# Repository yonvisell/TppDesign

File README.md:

# Thermopneumatic tactile pixel display

A 3 × 3 fingertip display uses electrically heated air cavities to deflect a silicone membrane at selected pixels. A 6 V driver controls the passive tactile array through ten conductors.

Max Linnander, Yon Visell, “Thermopneumatic Pixels: Fast, Localized, Robust, Low-Voltage Touch Feedback,” *IEEE Transactions on Haptics*, 2026. [journal](https://ieeexplore.ieee.org/document/11771129) · [arxiv](https://arxiv.org/abs/2603.16750)

**[Owner design book (PDF)](Owner-design-book.pdf)** · Revision L. System specifications, assembly drawings, model-based temperature control, predicted pressure response and complete client API.

| Subsystem | Design files |
|---|---|
| Tactile array | [Drawings](head/TA-drawings.pdf) · [Full-size templates](head/Lab-templates-1to1.pdf) · [STEP models](head/Mechanical-CAD.zip) · [Fabrication packages](head/jobs) |
| Driver board | [Schematic](eb/Schematic.pdf) · [Assembly package](eb/EB-supplier.zip) · [Firmware and installation](firmware/Controller.md) |
| Client interface | [OSC over UDP](software/OSC.md) · [Python client](software/client.py). Unit 1 uses the address prefix `/tpp/ta/1`. |
| Purchasing | [Bill of materials](purchasing/Integrated-BOM.csv) · [Build budget](purchasing/Build-budget.xlsx) |

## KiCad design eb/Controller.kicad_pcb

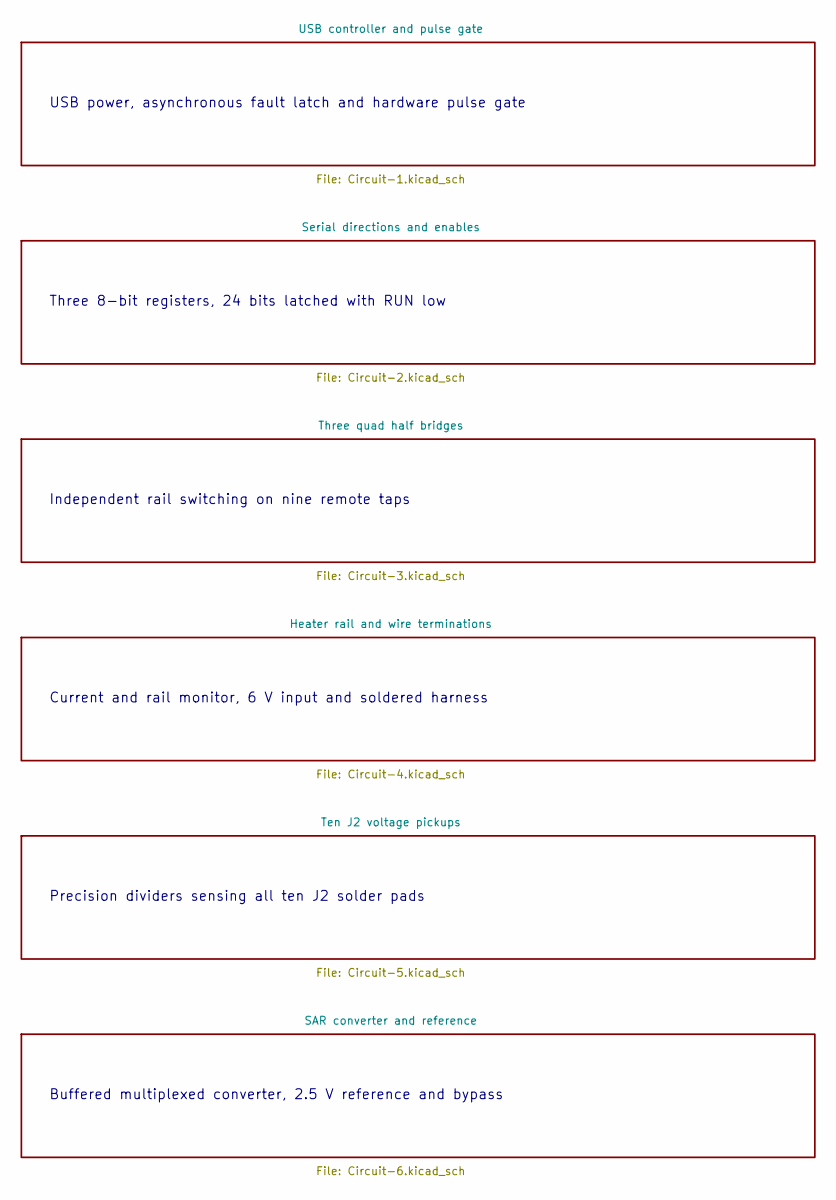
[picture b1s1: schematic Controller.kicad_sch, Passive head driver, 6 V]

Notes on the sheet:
USB power, asynchronous fault latch and hardware pulse gate
Three 8-bit registers, 24 bits latched with RUN low
Independent rail switching on nine remote taps
Current and rail monitor, 6 V input and soldered harness
Precision dividers sensing all ten J2 solder pads
Buffered multiplexed converter, 2.5 V reference and bypass

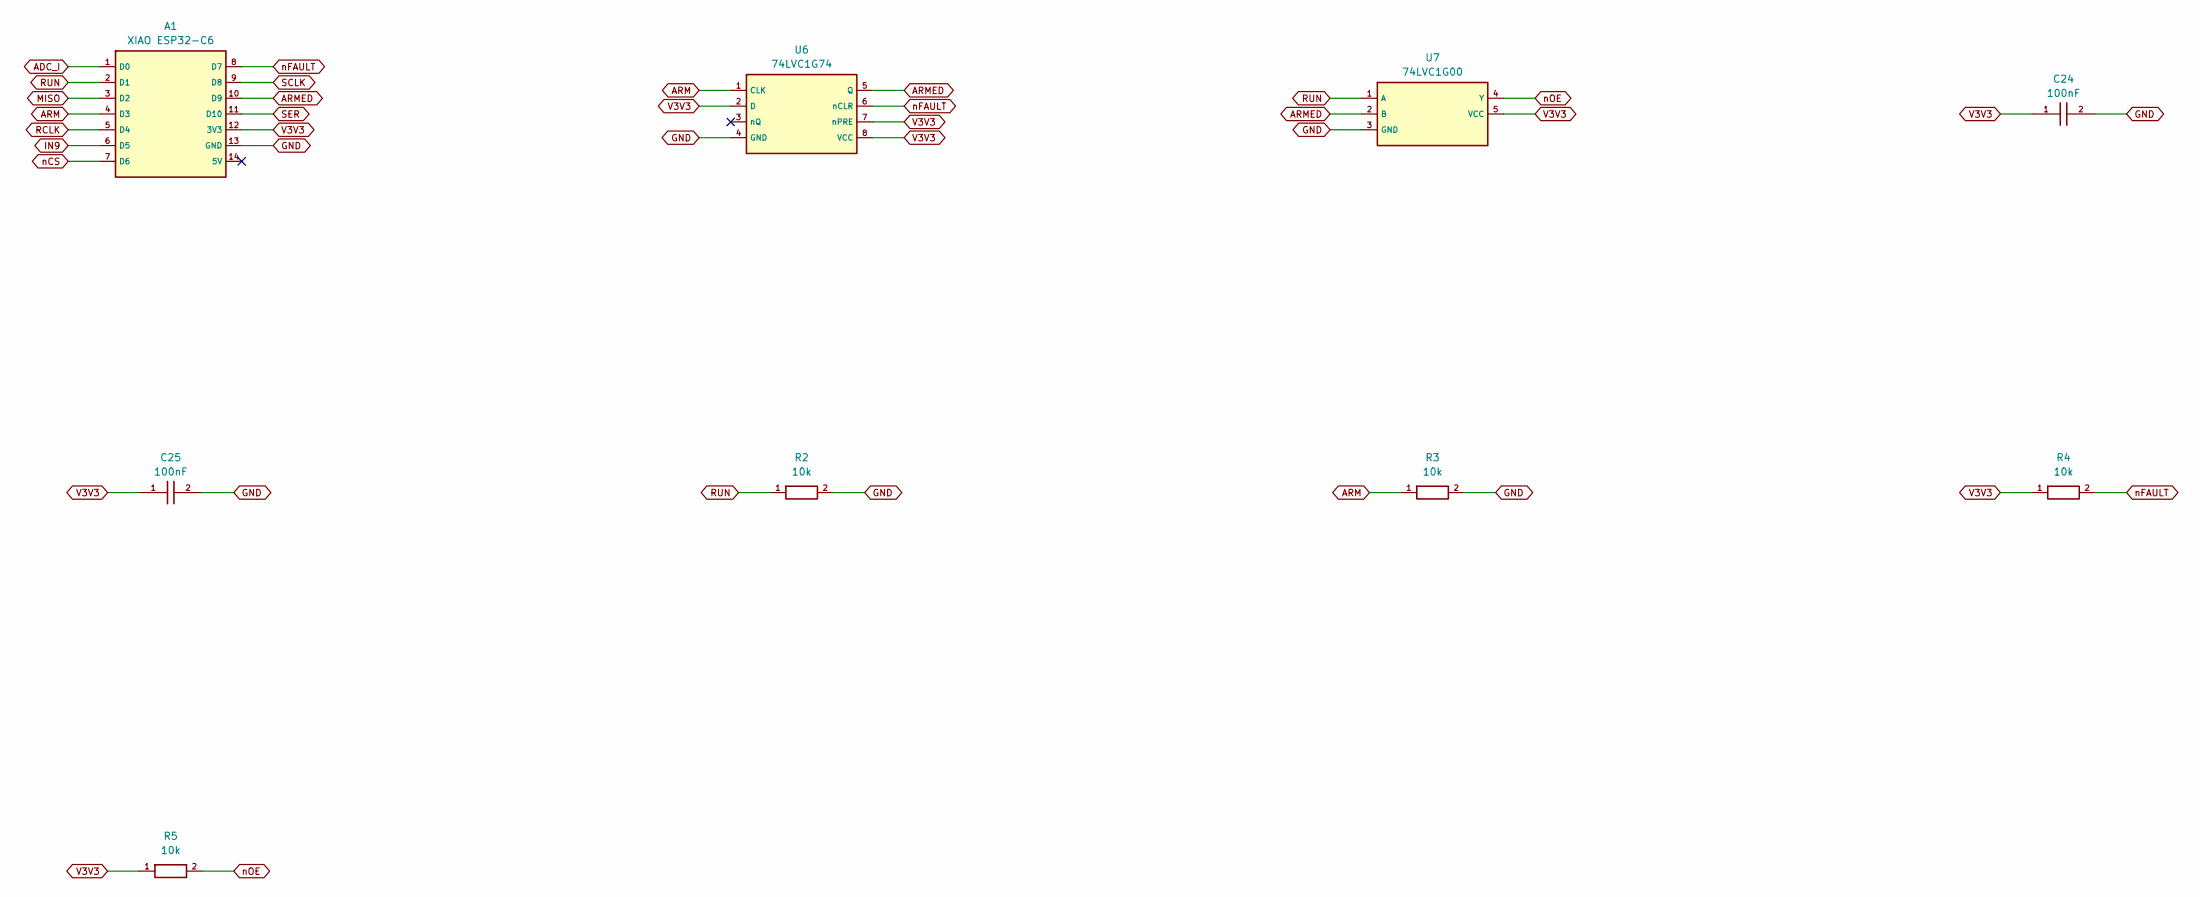
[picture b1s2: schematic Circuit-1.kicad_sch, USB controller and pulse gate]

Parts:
A1: XIAO ESP32-C6; XIAO-C6; MPN 113991254
C24, C25: 100nF; C_0603_1608Metric; MPN CC0603KRX7R9BB104
R2, R3, R4, R5: 10k; R_0603_1608Metric; MPN 0603WAF1002T5E
U6: 74LVC1G74; VSSOP-8_2.3x2mm_P0.5mm; MPN SN74LVC1G74DCUR
U7: 74LVC1G00; SOT-23-5; MPN SN74LVC1G00DBVR

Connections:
ADC_I: A1.1 (D0); also elsewhere on the board
ARM: A1.4 (D3), R3.1, U6.1 (CLK)
ARMED: A1.10 (D9), U6.5 (Q), U7.2 (B)
GND: A1.13 (GND), C24.2, C25.2, R2.2, R3.2, U6.4 (GND), U7.3 (GND); also elsewhere on the board
IN9: A1.6 (D5); also elsewhere on the board
MISO: A1.3 (D2); also elsewhere on the board
RCLK: A1.5 (D4); also elsewhere on the board
RUN: A1.2 (D1), R2.1, U7.1 (A)
SCLK: A1.9 (D8); also elsewhere on the board
SER: A1.11 (D10); also elsewhere on the board
V3V3: A1.12 (3V3), C24.1, C25.1, R4.1, R5.1, U6.2 (D), U6.7 (nPRE), U6.8 (VCC), U7.5 (VCC); also elsewhere on the board
nCS: A1.7 (D6); also elsewhere on the board
nFAULT: A1.8 (D7), R4.2, U6.6 (nCLR); also elsewhere on the board
nOE: R5.2, U7.4 (Y); also elsewhere on the board

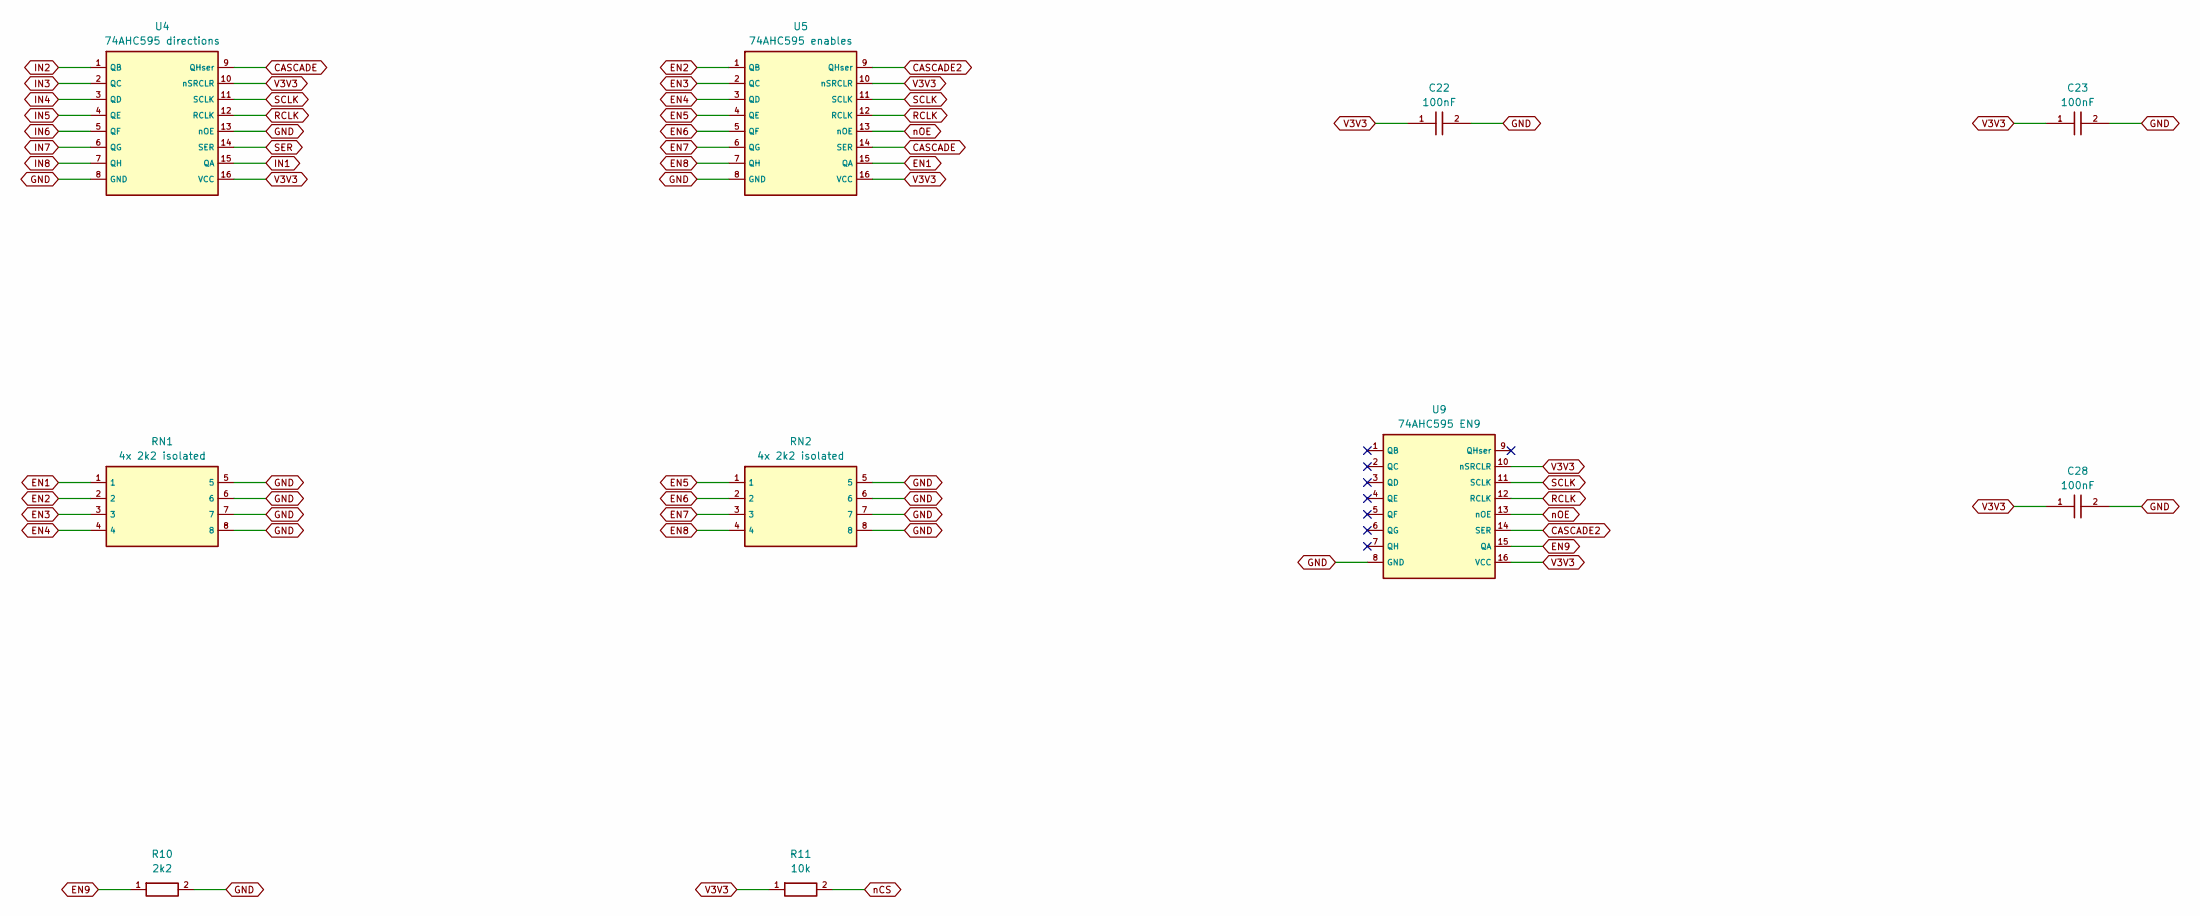
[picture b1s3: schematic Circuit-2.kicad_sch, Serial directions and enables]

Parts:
C22, C23, C28: 100nF; C_0603_1608Metric; MPN CC0603KRX7R9BB104
R10: 2k2; R_0603_1608Metric; MPN 0603WAF2201T5E
R11: 10k; R_0603_1608Metric; MPN 0603WAF1002T5E
RN1, RN2: 4x 2k2 isolated; R_Array_Convex_4x0603; MPN YC164-FR-072K2L
U4: 74AHC595 directions; TSSOP-16_4.4x5mm_P0.65mm; MPN SN74AHC595PWR
U5: 74AHC595 enables; TSSOP-16_4.4x5mm_P0.65mm; MPN SN74AHC595PWR
U9: 74AHC595 EN9; TSSOP-16_4.4x5mm_P0.65mm; MPN SN74AHC595PWR

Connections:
CASCADE: U4.9 (QHser), U5.14 (SER)
CASCADE2: U5.9 (QHser), U9.14 (SER)
EN1: RN1.1, U5.15 (QA); also elsewhere on the board
EN2: RN1.2, U5.1 (QB); also elsewhere on the board
EN3: RN1.3, U5.2 (QC); also elsewhere on the board
EN4: RN1.4, U5.3 (QD); also elsewhere on the board
EN5: RN2.1, U5.4 (QE); also elsewhere on the board
EN6: RN2.2, U5.5 (QF); also elsewhere on the board
EN7: RN2.3, U5.6 (QG); also elsewhere on the board
EN8: RN2.4, U5.7 (QH); also elsewhere on the board
EN9: R10.1, U9.15 (QA); also elsewhere on the board
GND: C22.2, C23.2, C28.2, R10.2, RN1.5, RN1.6, RN1.7, RN1.8, RN2.5, RN2.6, RN2.7, RN2.8, U4.8 (GND), U4.13 (nOE), U5.8 (GND), U9.8 (GND); also elsewhere on the board
IN1: U4.15 (QA); also elsewhere on the board
IN2: U4.1 (QB); also elsewhere on the board
IN3: U4.2 (QC); also elsewhere on the board
IN4: U4.3 (QD); also elsewhere on the board
IN5: U4.4 (QE); also elsewhere on the board
IN6: U4.5 (QF); also elsewhere on the board
IN7: U4.6 (QG); also elsewhere on the board
IN8: U4.7 (QH); also elsewhere on the board
RCLK: U4.12 (RCLK), U5.12 (RCLK), U9.12 (RCLK); also elsewhere on the board
SCLK: U4.11 (SCLK), U5.11 (SCLK), U9.11 (SCLK); also elsewhere on the board
SER: U4.14 (SER); also elsewhere on the board
V3V3: C22.1, C23.1, C28.1, R11.1, U4.10 (nSRCLR), U4.16 (VCC), U5.10 (nSRCLR), U5.16 (VCC), U9.10 (nSRCLR), U9.16 (VCC); also elsewhere on the board
nCS: R11.2; also elsewhere on the board
nOE: U5.13 (nOE), U9.13 (nOE); also elsewhere on the board

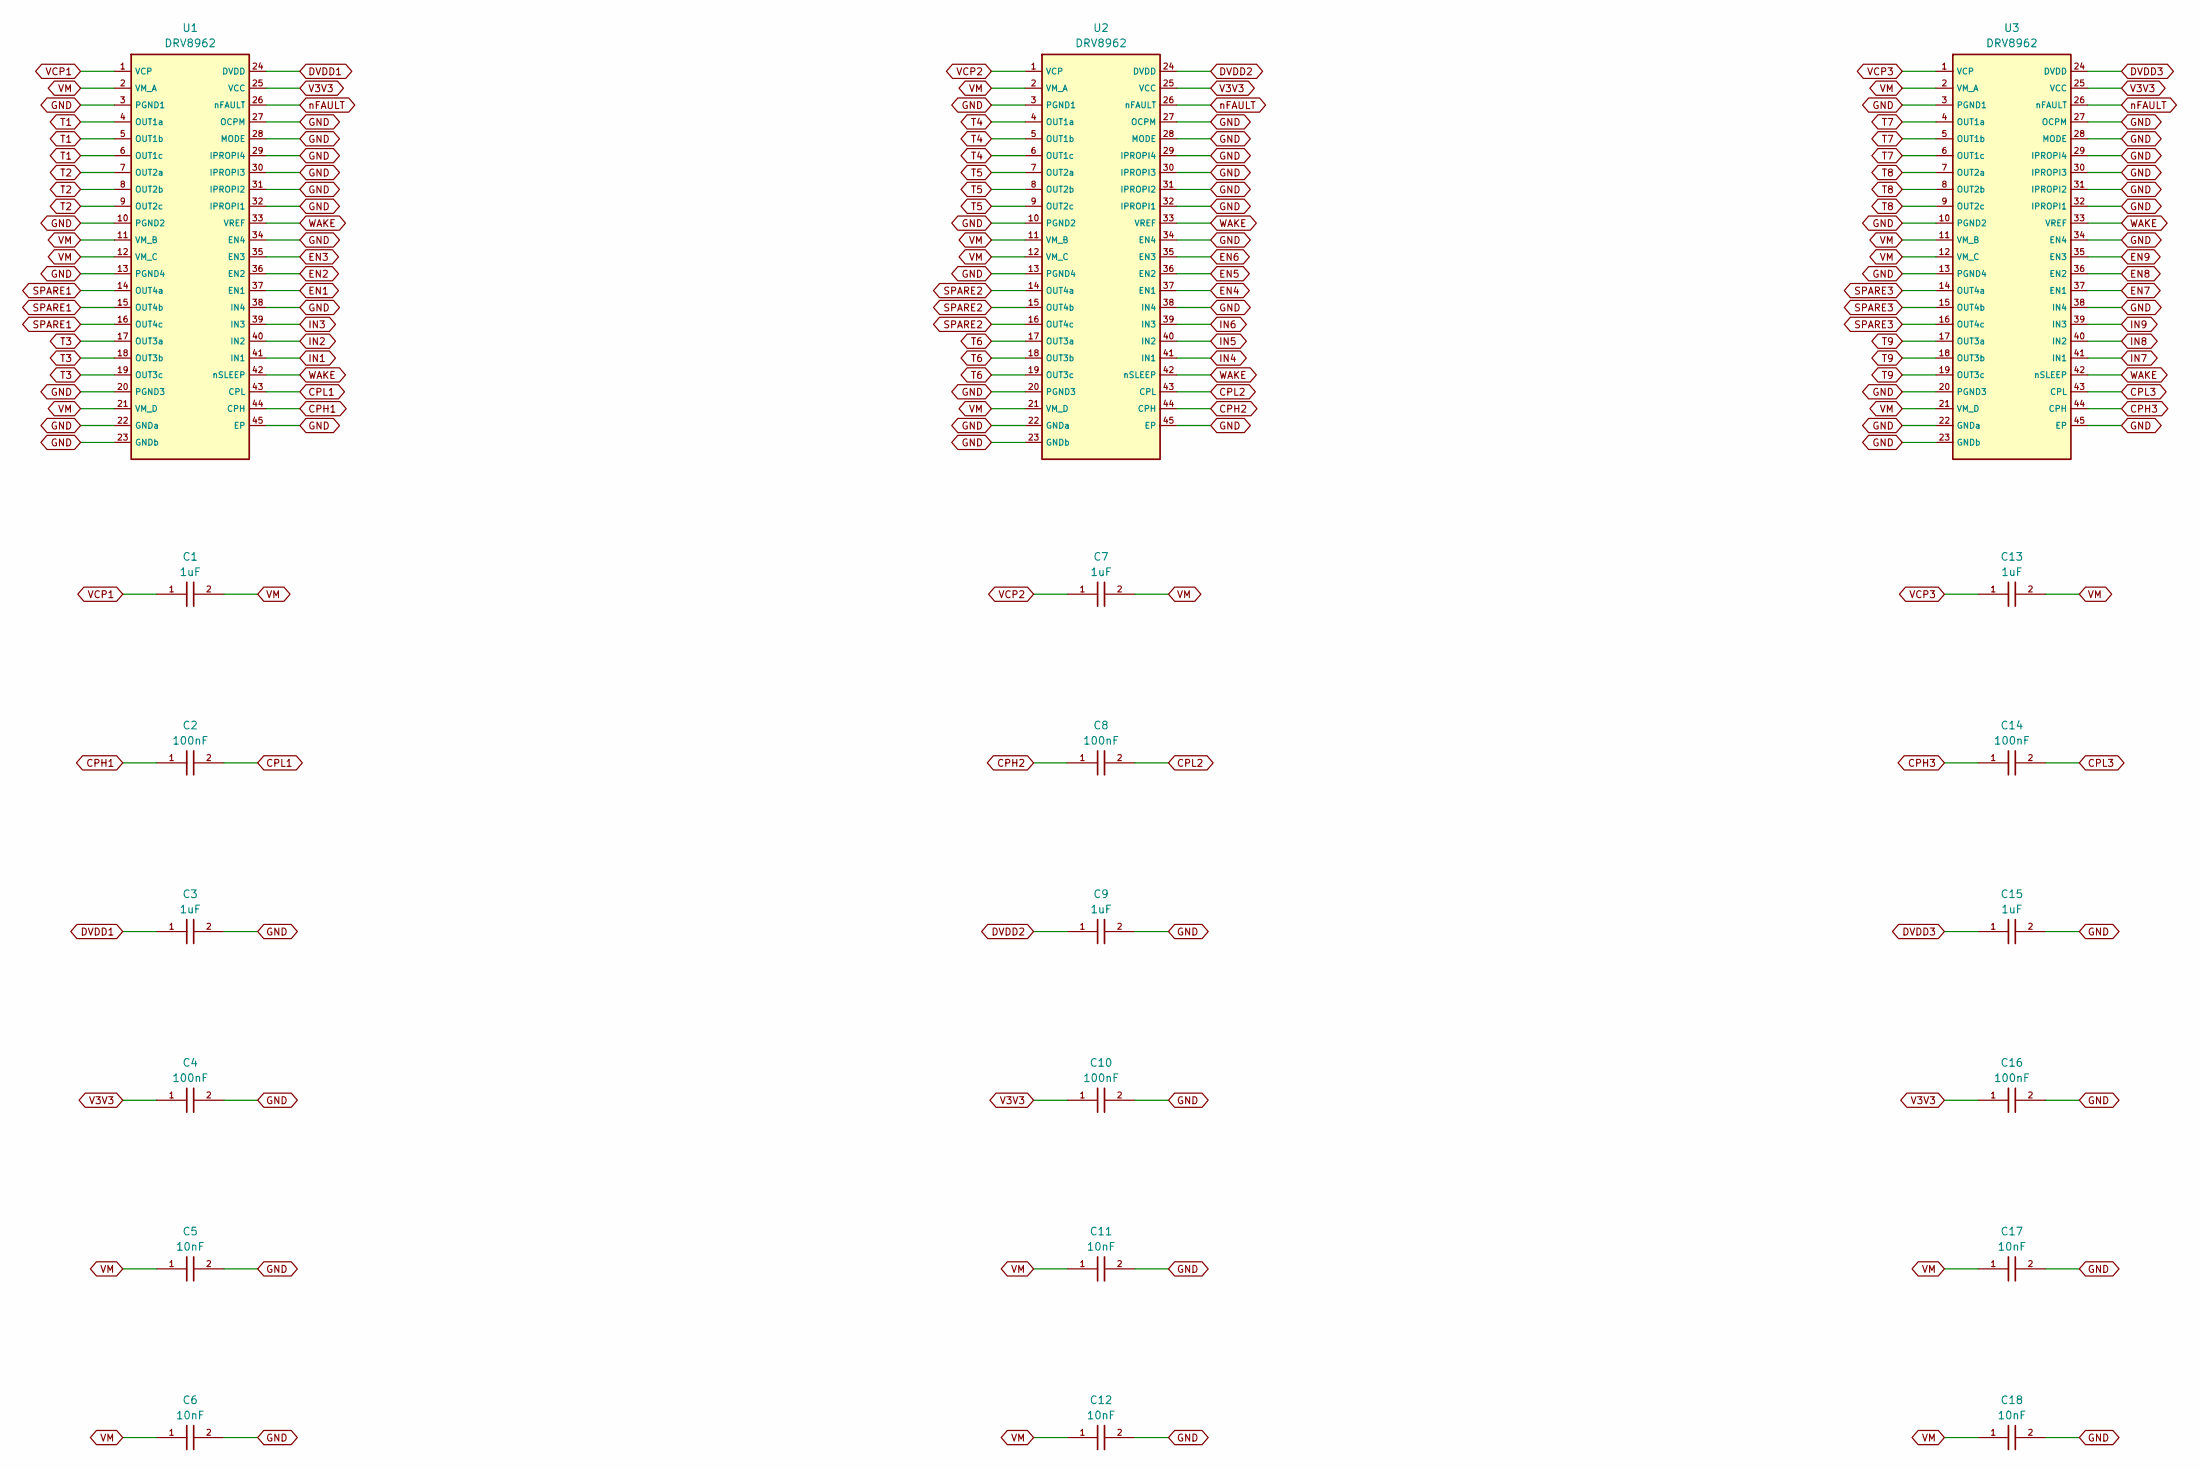
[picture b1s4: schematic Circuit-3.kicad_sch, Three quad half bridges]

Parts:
C1, C3, C7, C9, C13, C15: 1uF; C_0603_1608Metric; MPN CC0603KRX7R7BB105
C2, C4, C8, C10, C14, C16: 100nF; C_0603_1608Metric; MPN CC0603KRX7R9BB104
C5, C6, C11, C12, C17, C18: 10nF; C_0603_1608Metric; MPN GRM188R71H103KA01D
U1, U2, U3: DRV8962; DDW0044E; MPN DRV8962DDWR

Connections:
CPH1: C2.1, U1.44 (CPH)
CPH2: C8.1, U2.44 (CPH)
CPH3: C14.1, U3.44 (CPH)
CPL1: C2.2, U1.43 (CPL)
CPL2: C8.2, U2.43 (CPL)
CPL3: C14.2, U3.43 (CPL)
DVDD1: C3.1, U1.24 (DVDD)
DVDD2: C9.1, U2.24 (DVDD)
DVDD3: C15.1, U3.24 (DVDD)
EN1: U1.37 (EN1); also elsewhere on the board
EN2: U1.36 (EN2); also elsewhere on the board
EN3: U1.35 (EN3); also elsewhere on the board
EN4: U2.37 (EN1); also elsewhere on the board
EN5: U2.36 (EN2); also elsewhere on the board
EN6: U2.35 (EN3); also elsewhere on the board
EN7: U3.37 (EN1); also elsewhere on the board
EN8: U3.36 (EN2); also elsewhere on the board
EN9: U3.35 (EN3); also elsewhere on the board
GND: C3.2, C4.2, C5.2, C6.2, C9.2, C10.2, C11.2, C12.2, C15.2, C16.2, C17.2, C18.2, U1.3 (PGND1), U1.10 (PGND2), U1.13 (PGND4), U1.20 (PGND3), U1.22 (GNDa), U1.23 (GNDb), U1.27 (OCPM), U1.28 (MODE), U1.29 (IPROPI4), U1.30 (IPROPI3), U1.31 (IPROPI2), U1.32 (IPROPI1), U1.34 (EN4), U1.38 (IN4), U1.45 (EP), U2.3 (PGND1), U2.10 (PGND2), U2.13 (PGND4), U2.20 (PGND3), U2.22 (GNDa), U2.23 (GNDb), U2.27 (OCPM), U2.28 (MODE), U2.29 (IPROPI4), U2.30 (IPROPI3), U2.31 (IPROPI2), U2.32 (IPROPI1), U2.34 (EN4), U2.38 (IN4), U2.45 (EP), U3.3 (PGND1), U3.10 (PGND2), U3.13 (PGND4), U3.20 (PGND3), U3.22 (GNDa), U3.23 (GNDb), U3.27 (OCPM), U3.28 (MODE), U3.29 (IPROPI4), U3.30 (IPROPI3), U3.31 (IPROPI2), U3.32 (IPROPI1), U3.34 (EN4), U3.38 (IN4), U3.45 (EP); also elsewhere on the board
IN1: U1.41 (IN1); also elsewhere on the board
IN2: U1.40 (IN2); also elsewhere on the board
IN3: U1.39 (IN3); also elsewhere on the board
IN4: U2.41 (IN1); also elsewhere on the board
IN5: U2.40 (IN2); also elsewhere on the board
IN6: U2.39 (IN3); also elsewhere on the board
IN7: U3.41 (IN1); also elsewhere on the board
IN8: U3.40 (IN2); also elsewhere on the board
IN9: U3.39 (IN3); also elsewhere on the board
SPARE1: U1.14 (OUT4a), U1.15 (OUT4b), U1.16 (OUT4c)
SPARE2: U2.14 (OUT4a), U2.15 (OUT4b), U2.16 (OUT4c)
SPARE3: U3.14 (OUT4a), U3.15 (OUT4b), U3.16 (OUT4c)
T1: U1.4 (OUT1a), U1.5 (OUT1b), U1.6 (OUT1c); also elsewhere on the board
T2: U1.7 (OUT2a), U1.8 (OUT2b), U1.9 (OUT2c); also elsewhere on the board
T3: U1.17 (OUT3a), U1.18 (OUT3b), U1.19 (OUT3c); also elsewhere on the board
T4: U2.4 (OUT1a), U2.5 (OUT1b), U2.6 (OUT1c); also elsewhere on the board
T5: U2.7 (OUT2a), U2.8 (OUT2b), U2.9 (OUT2c); also elsewhere on the board
T6: U2.17 (OUT3a), U2.18 (OUT3b), U2.19 (OUT3c); also elsewhere on the board
T7: U3.4 (OUT1a), U3.5 (OUT1b), U3.6 (OUT1c); also elsewhere on the board
T8: U3.7 (OUT2a), U3.8 (OUT2b), U3.9 (OUT2c); also elsewhere on the board
T9: U3.17 (OUT3a), U3.18 (OUT3b), U3.19 (OUT3c); also elsewhere on the board
V3V3: C4.1, C10.1, C16.1, U1.25 (VCC), U2.25 (VCC), U3.25 (VCC); also elsewhere on the board
VCP1: C1.1, U1.1 (VCP)
VCP2: C7.1, U2.1 (VCP)
VCP3: C13.1, U3.1 (VCP)
VM: C1.2, C5.1, C6.1, C7.2, C11.1, C12.1, C13.2, C17.1, C18.1, U1.2 (VM_A), U1.11 (VM_B), U1.12 (VM_C), U1.21 (VM_D), U2.2 (VM_A), U2.11 (VM_B), U2.12 (VM_C), U2.21 (VM_D), U3.2 (VM_A), U3.11 (VM_B), U3.12 (VM_C), U3.21 (VM_D); also elsewhere on the board
WAKE: U1.33 (VREF), U1.42 (nSLEEP), U2.33 (VREF), U2.42 (nSLEEP), U3.33 (VREF), U3.42 (nSLEEP); also elsewhere on the board
nFAULT: U1.26 (nFAULT), U2.26 (nFAULT), U3.26 (nFAULT); also elsewhere on the board

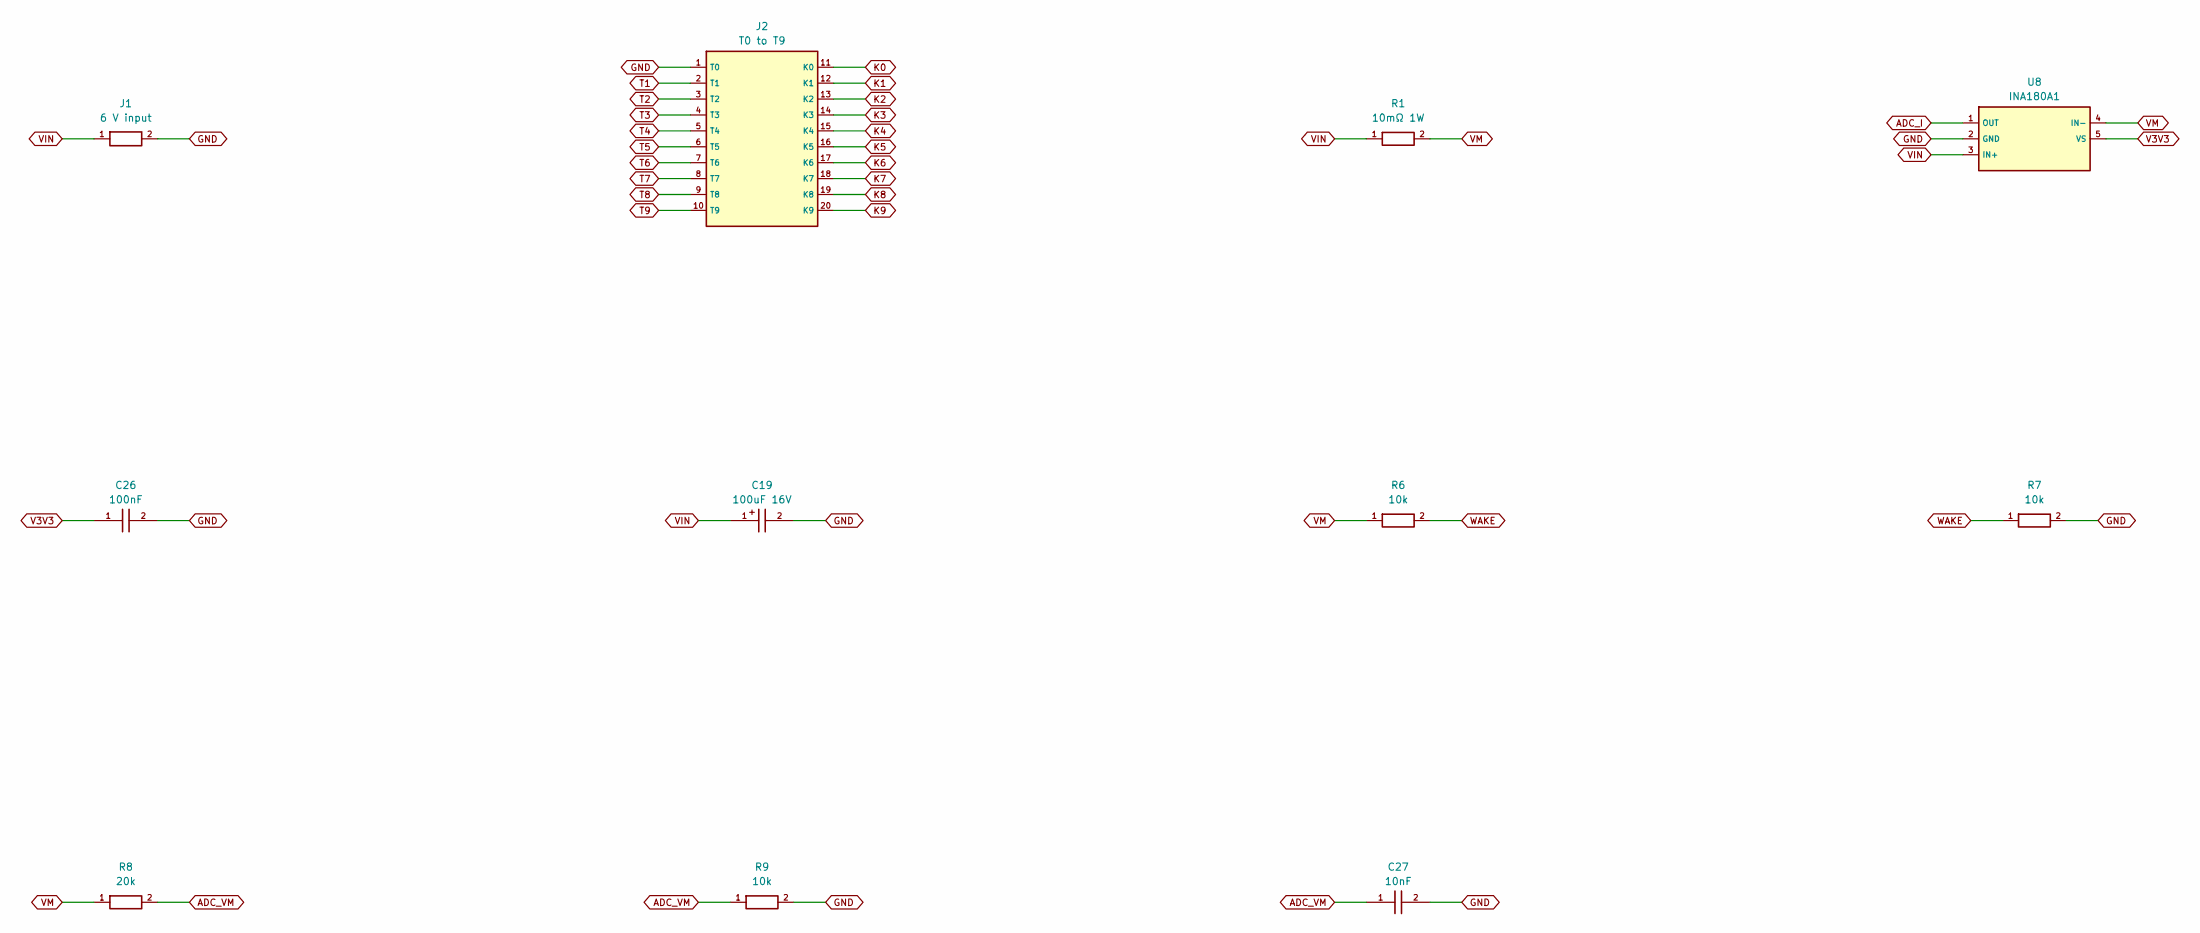
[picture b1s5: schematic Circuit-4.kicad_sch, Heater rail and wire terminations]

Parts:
C19: 100uF 16V; CP_Elec_6.3x5.8; MPN EEEFK1C101P
C26: 100nF; C_0603_1608Metric; MPN CC0603KRX7R9BB104
C27: 10nF; C_0603_1608Metric; MPN GRM188R71H103KA01D
J1: 6 V input; Power2; MPN PCB solder holes
J2: T0 to T9; Taps10; MPN PCB solder holes
R1: 10mΩ 1W; R_2512_6332Metric; MPN WSL2512R0100FEA
R6, R7, R9: 10k; R_0603_1608Metric; MPN 0603WAF1002T5E
R8: 20k; R_0603_1608Metric; MPN 0603WAF2002T5E
U8: INA180A1; SOT-23-5; MPN INA180A1IDBVR

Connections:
ADC_I: U8.1 (OUT); also elsewhere on the board
ADC_VM: C27.1, R8.2, R9.1; also elsewhere on the board
GND: C19.2 (-), C26.2, C27.2, J1.2 (RETURN), J2.1 (T0), R7.2, R9.2, U8.2 (GND); also elsewhere on the board
K0: J2.11 (K0); also elsewhere on the board
K1: J2.12 (K1); also elsewhere on the board
K2: J2.13 (K2); also elsewhere on the board
K3: J2.14 (K3); also elsewhere on the board
K4: J2.15 (K4); also elsewhere on the board
K5: J2.16 (K5); also elsewhere on the board
K6: J2.17 (K6); also elsewhere on the board
K7: J2.18 (K7); also elsewhere on the board
K8: J2.19 (K8); also elsewhere on the board
K9: J2.20 (K9); also elsewhere on the board
T1: J2.2 (T1); also elsewhere on the board
T2: J2.3 (T2); also elsewhere on the board
T3: J2.4 (T3); also elsewhere on the board
T4: J2.5 (T4); also elsewhere on the board
T5: J2.6 (T5); also elsewhere on the board
T6: J2.7 (T6); also elsewhere on the board
T7: J2.8 (T7); also elsewhere on the board
T8: J2.9 (T8); also elsewhere on the board
T9: J2.10 (T9); also elsewhere on the board
V3V3: C26.1, U8.5 (VS); also elsewhere on the board
VIN: C19.1 (+), J1.1 (PLUS), R1.1, U8.3 (IN+)
VM: R1.2, R6.1, R8.1, U8.4 (IN-); also elsewhere on the board
WAKE: R6.2, R7.1; also elsewhere on the board

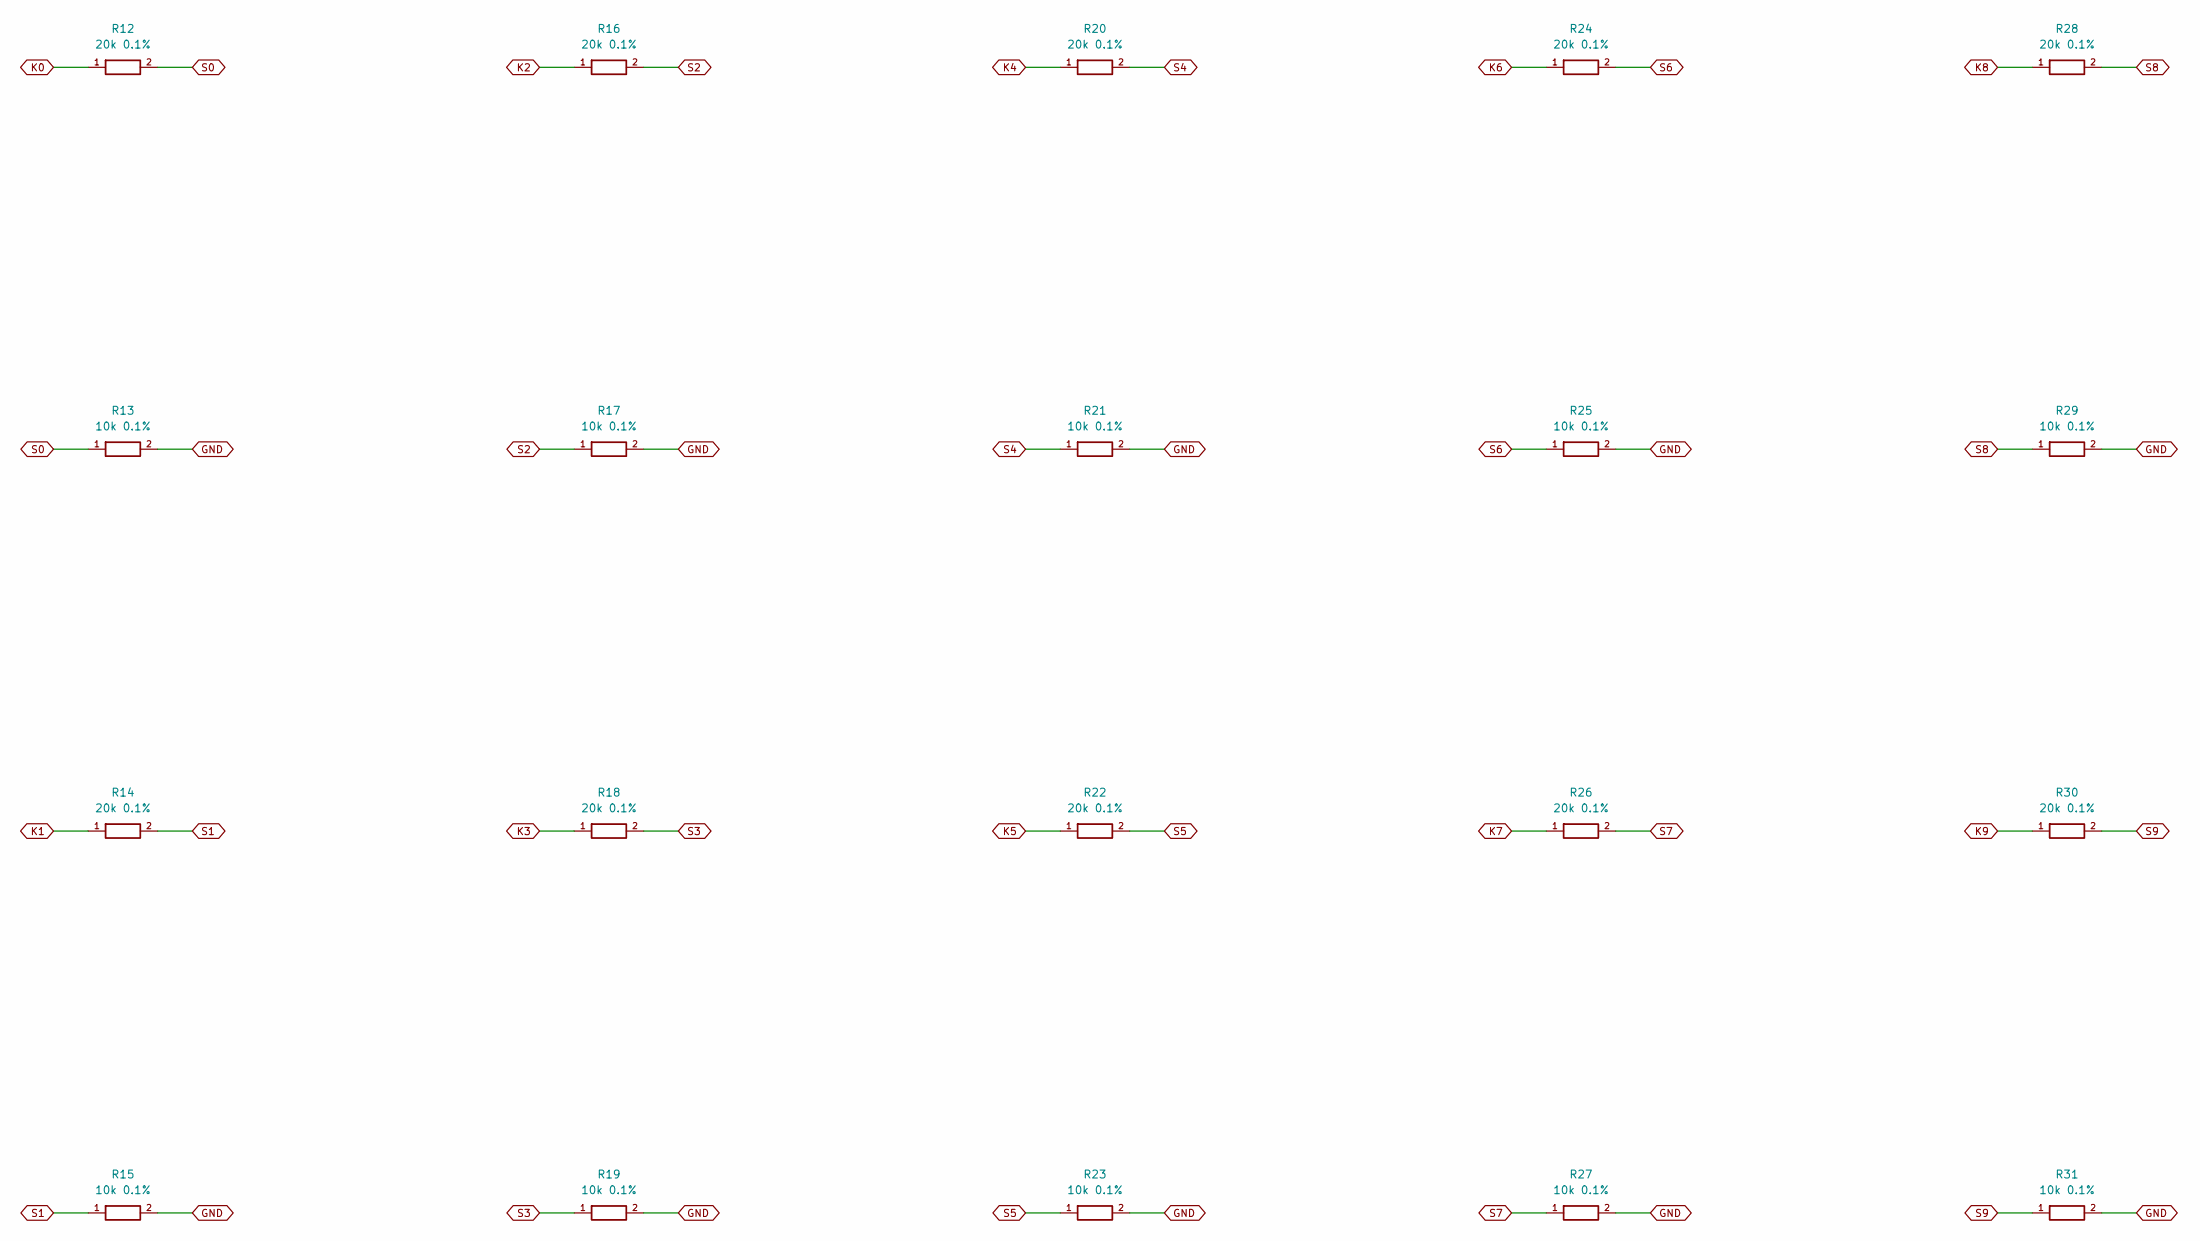
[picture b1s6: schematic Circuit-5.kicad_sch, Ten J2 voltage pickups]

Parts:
R12, R14, R16, R18, R20, R22, R24, R26, R28, R30: 20k 0.1%; R_0603_1608Metric; MPN RT0603BRD0720KL
R13, R15, R17, R19, R21, R23, R25, R27, R29, R31: 10k 0.1%; R_0603_1608Metric; MPN RT0603BRD0710KL

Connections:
GND: R13.2, R15.2, R17.2, R19.2, R21.2, R23.2, R25.2, R27.2, R29.2, R31.2; also elsewhere on the board
K0: R12.1; also elsewhere on the board
K1: R14.1; also elsewhere on the board
K2: R16.1; also elsewhere on the board
K3: R18.1; also elsewhere on the board
K4: R20.1; also elsewhere on the board
K5: R22.1; also elsewhere on the board
K6: R24.1; also elsewhere on the board
K7: R26.1; also elsewhere on the board
K8: R28.1; also elsewhere on the board
K9: R30.1; also elsewhere on the board
S0: R12.2, R13.1; also elsewhere on the board
S1: R14.2, R15.1; also elsewhere on the board
S2: R16.2, R17.1; also elsewhere on the board
S3: R18.2, R19.1; also elsewhere on the board
S4: R20.2, R21.1; also elsewhere on the board
S5: R22.2, R23.1; also elsewhere on the board
S6: R24.2, R25.1; also elsewhere on the board
S7: R26.2, R27.1; also elsewhere on the board
S8: R28.2, R29.1; also elsewhere on the board
S9: R30.2, R31.1; also elsewhere on the board

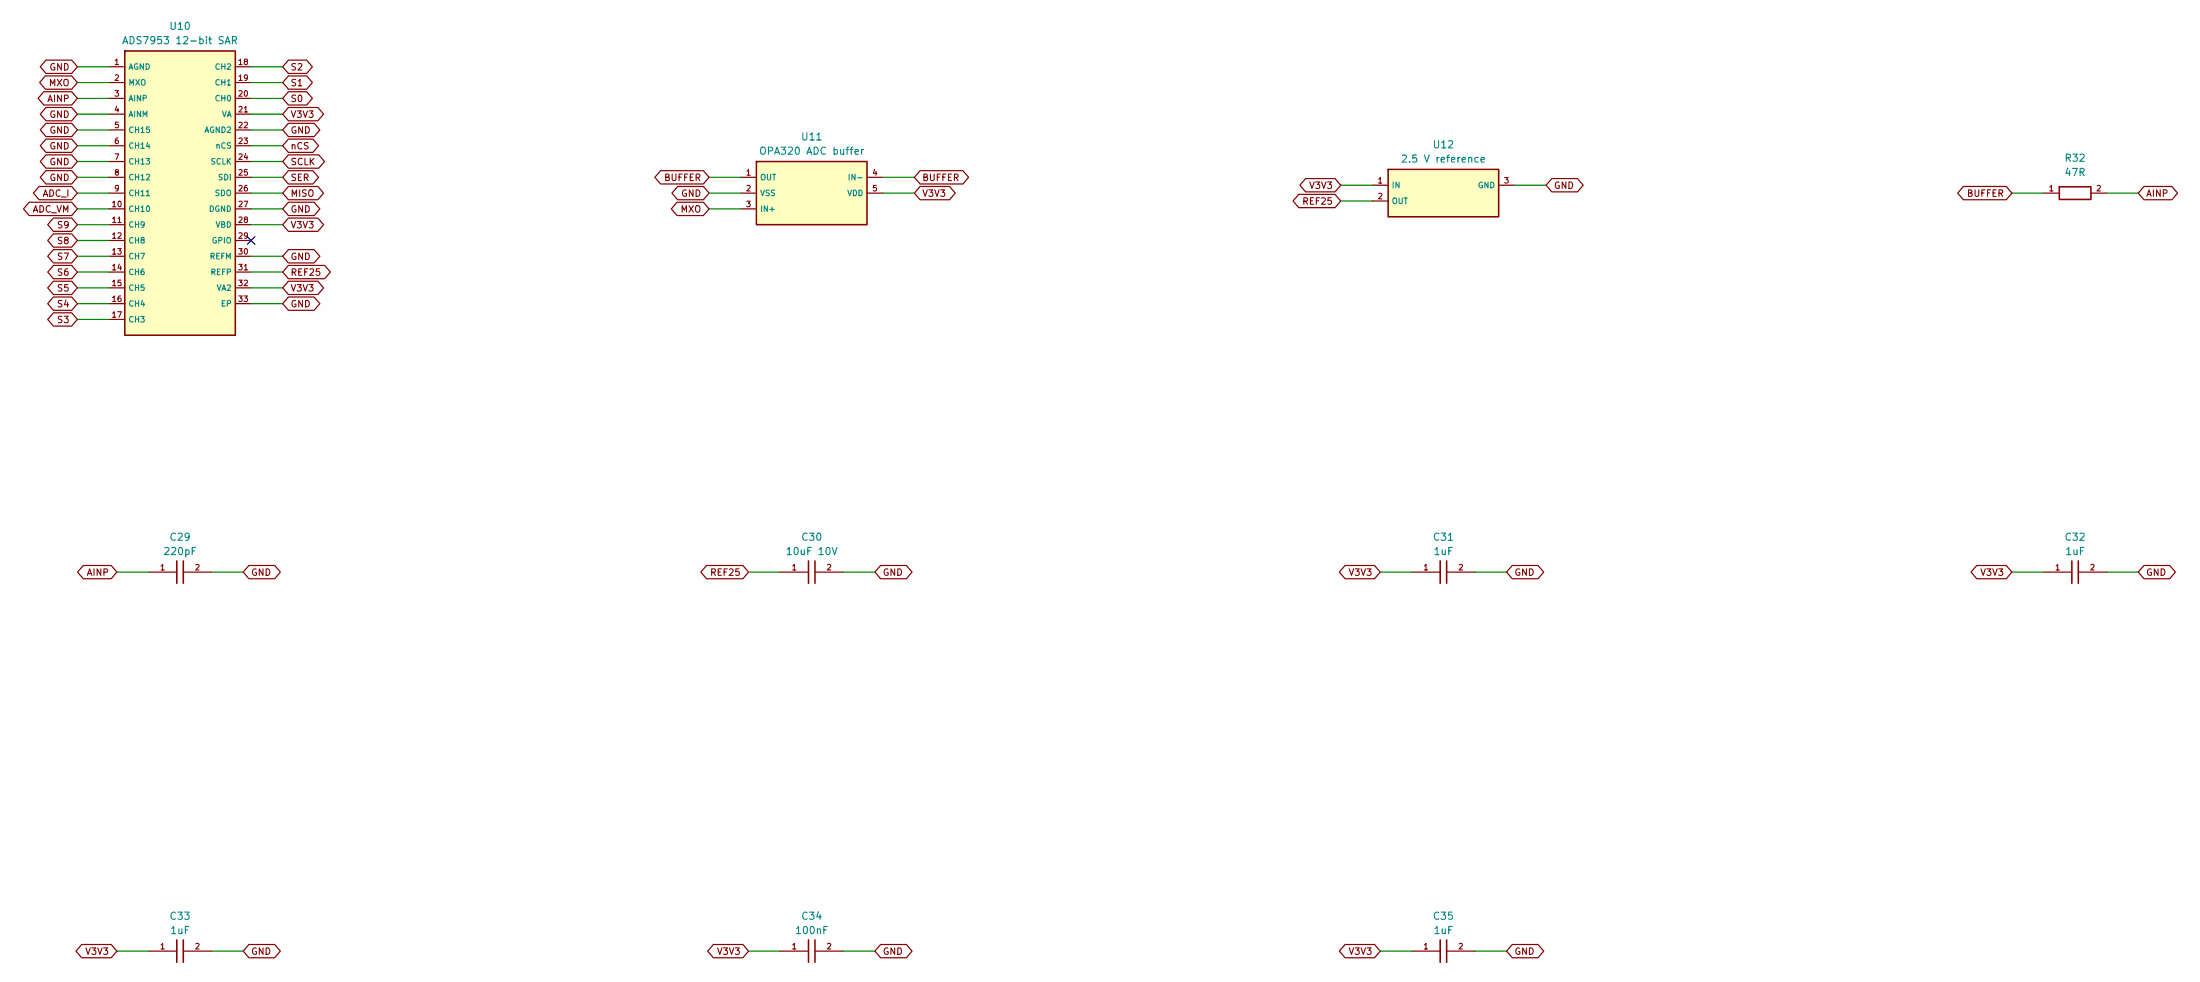
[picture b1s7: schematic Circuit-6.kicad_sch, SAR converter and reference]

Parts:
C29: 220pF; C_0402_1005Metric; MPN CL05C221JB5NNNC
C30: 10uF 10V; C_0805_2012Metric; MPN GRM21BR71A106KE51L
C31, C32, C35: 1uF; C_0603_1608Metric; MPN CC0603KRX7R7BB105
C33: 1uF; C_0402_1005Metric; MPN GRM155R61A105KE15D
C34: 100nF; C_0603_1608Metric; MPN CC0603KRX7R9BB104
R32: 47R; R_0603_1608Metric; MPN 0603WAF470JT5E
U10: ADS7953 12-bit SAR; VQFN-32-1EP_5x5mm_P0.5mm_EP3.15x3.15mm; MPN ADS7953SRHBR
U11: OPA320 ADC buffer; SOT-23-5; MPN OPA320AIDBVR
U12: 2.5 V reference; SOT-23; MPN REF3125AIDBZR

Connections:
ADC_I: U10.9 (CH11); also elsewhere on the board
ADC_VM: U10.10 (CH10); also elsewhere on the board
AINP: C29.1, R32.2, U10.3 (AINP)
BUFFER: R32.1, U11.1 (OUT), U11.4 (IN-)
GND: C29.2, C30.2, C31.2, C32.2, C33.2, C34.2, C35.2, U10.1 (AGND), U10.4 (AINM), U10.5 (CH15), U10.6 (CH14), U10.7 (CH13), U10.8 (CH12), U10.22 (AGND2), U10.27 (DGND), U10.30 (REFM), U10.33 (EP), U11.2 (VSS), U12.3 (GND); also elsewhere on the board
MISO: U10.26 (SDO); also elsewhere on the board
MXO: U10.2 (MXO), U11.3 (IN+)
REF25: C30.1, U10.31 (REFP), U12.2 (OUT)
S0: U10.20 (CH0); also elsewhere on the board
S1: U10.19 (CH1); also elsewhere on the board
S2: U10.18 (CH2); also elsewhere on the board
S3: U10.17 (CH3); also elsewhere on the board
S4: U10.16 (CH4); also elsewhere on the board
S5: U10.15 (CH5); also elsewhere on the board
S6: U10.14 (CH6); also elsewhere on the board
S7: U10.13 (CH7); also elsewhere on the board
S8: U10.12 (CH8); also elsewhere on the board
S9: U10.11 (CH9); also elsewhere on the board
SCLK: U10.24 (SCLK); also elsewhere on the board
SER: U10.25 (SDI); also elsewhere on the board
V3V3: C31.1, C32.1, C33.1, C34.1, C35.1, U10.21 (VA), U10.28 (VBD), U10.32 (VA2), U11.5 (VDD), U12.1 (IN); also elsewhere on the board
nCS: U10.23 (nCS); also elsewhere on the board
